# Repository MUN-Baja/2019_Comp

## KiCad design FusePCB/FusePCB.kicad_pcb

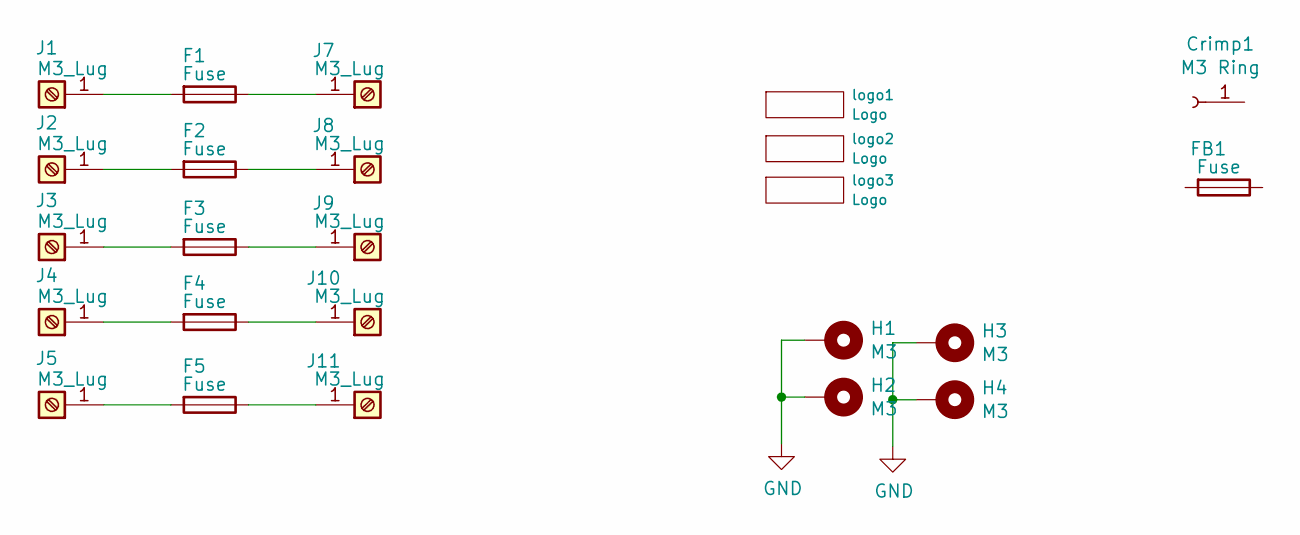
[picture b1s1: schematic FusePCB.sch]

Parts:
Crimp1: M3 Ring
F1, F2, F3, F4, F5: Fuse; Fuse_ATC_ATO_BLADE
FB1: Fuse
H1, H2, H3, H4: M3; 3.4mm_mounting_hole_SILK
J1, J2, J3, J4, J5, J7, J8, J9, J10, J11: M3_Lug; LVDC_M3_Lug
logo1, logo2: Logo; SN_BLOCK
logo3: Logo; KiCad-Logo_8mm_SilkScreen

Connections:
GND: H1.1, H2.1, H3.1, H4.1
unnamed: F1.1, J7.1
unnamed: F1.2, J1.1
unnamed: F2.1, J8.1
unnamed: F2.2, J2.1
unnamed: F3.1, J9.1
unnamed: F3.2, J3.1
unnamed: F4.1, J10.1
unnamed: F4.2, J4.1
unnamed: F5.1, J11.1
unnamed: F5.2, J5.1

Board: 2 copper layers, 22 parts (1 on the bottom side), 11 nets, no tracks yet.

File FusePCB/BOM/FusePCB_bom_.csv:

Component,Description,Part,References,Value,Footprint,Quantity Per PCB,Datasheet
1,"Generic connector, single row, 01x01, script generated (kicad-library-utils/schlib/autogen/connector/)",Conn_01x01_Female,Crimp1,M3 Ring,,10,277-11117-ND
2,Fuse,Fuse,F1 F2 F3 F4 F5,Fuse,Fuse_ATC_ATO_BLADE,10,36-3522-ND
4,"Generic screw terminal, single row, 01x01, script generated (kicad-library-utils/schlib/autogen/connector/)",Screw_Terminal_01x01,J1 J2 J3 J4 J5 J7 J8 J9 J10 J11,M3_Lug,LVDC_M3_Lug,10,36-7771-ND
,,3A,,,,3,F4193-ND
,,10A,,,,2,F4199-ND
,,20A,,,,2,F4201-ND
,,5A,,,,1,F4197-ND
,,15A,,,,1,F4200-ND
,,40A,,,,1,F4203-ND
,,7.5A,,,,1,F4198-ND
,,1A,,,,2,F4191-ND
,,,,,,,
,,,,,,,
,,,,,,,
,,,,,,,
,,,,,,,
,,,,,,,
,,,,,,,
,,,,,,,
,,,,,,,
,,,,,,,
,,,,,,,
Component Groups:,6,,,,,,
Component Count:,20,,,,,,
Fitted Components:,20,,,,,,
Number of PCBs:,1,,,,,,
Total components:,20,,,,,,
Schematic Version:,,,,,,,
Schematic Date:,,,,,,,
BoM Date:,5/25/2019 2:43,,,,,,
Schematic Source:,C:\projects\BAJA\FusePCB\FusePCB.sch,,,,,,
KiCad Version:,Eeschema (5.0.2)-1,,,,,,

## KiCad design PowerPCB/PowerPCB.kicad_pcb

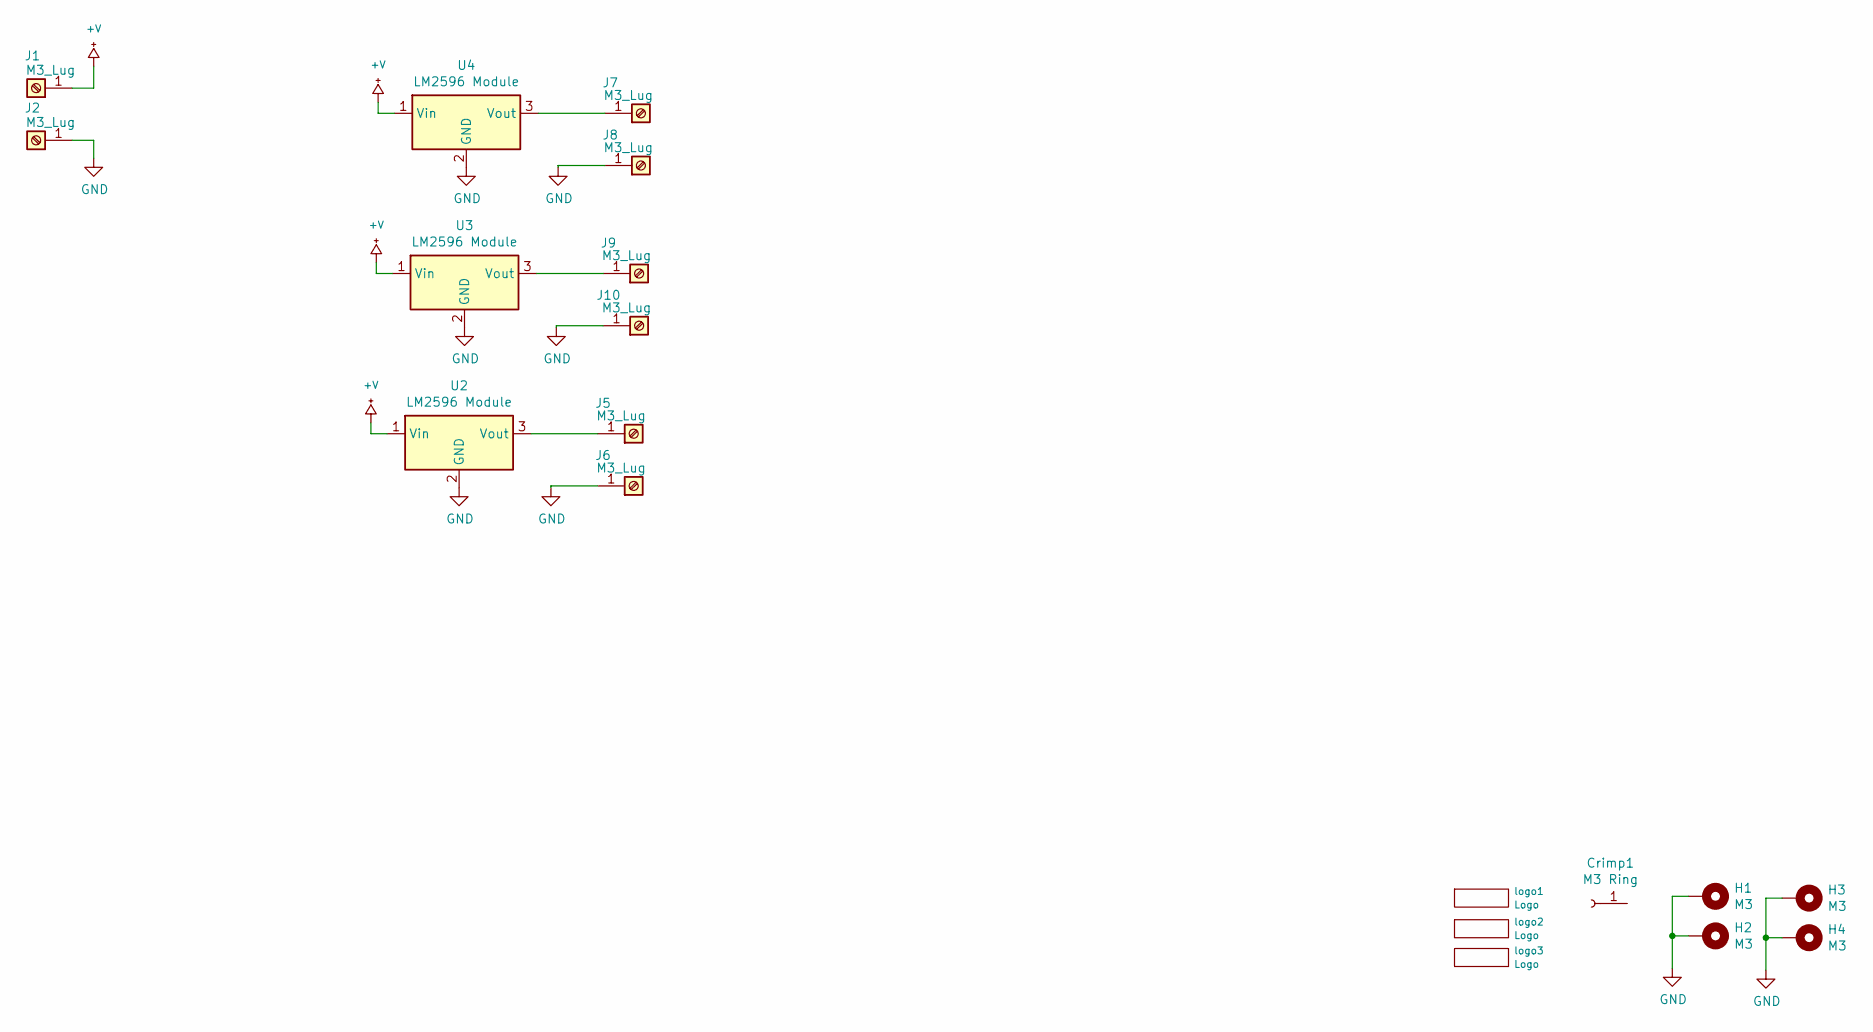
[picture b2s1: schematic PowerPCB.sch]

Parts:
Crimp1: M3 Ring
H1, H2, H3, H4: M3; 3.4mm_mounting_hole_SILK
J1, J2, J5, J6, J7, J8, J9, J10: M3_Lug; LVDC_M3_Lug
U2, U3, U4: LM2596 Module; LM2596_Module
logo1, logo2: Logo; SN_BLOCK
logo3: Logo; KiCad-Logo_8mm_SilkScreen

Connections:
+V: J1.1, U2.1 (Vin), U3.1 (Vin), U4.1 (Vin)
GND: H1.1, H2.1, H3.1, H4.1, J2.1, J6.1, J8.1, J10.1, U2.2 (GND), U3.2 (GND), U4.2 (GND)
unnamed: J5.1, U2.3 (Vout)
unnamed: J7.1, U4.3 (Vout)
unnamed: J9.1, U3.3 (Vout)

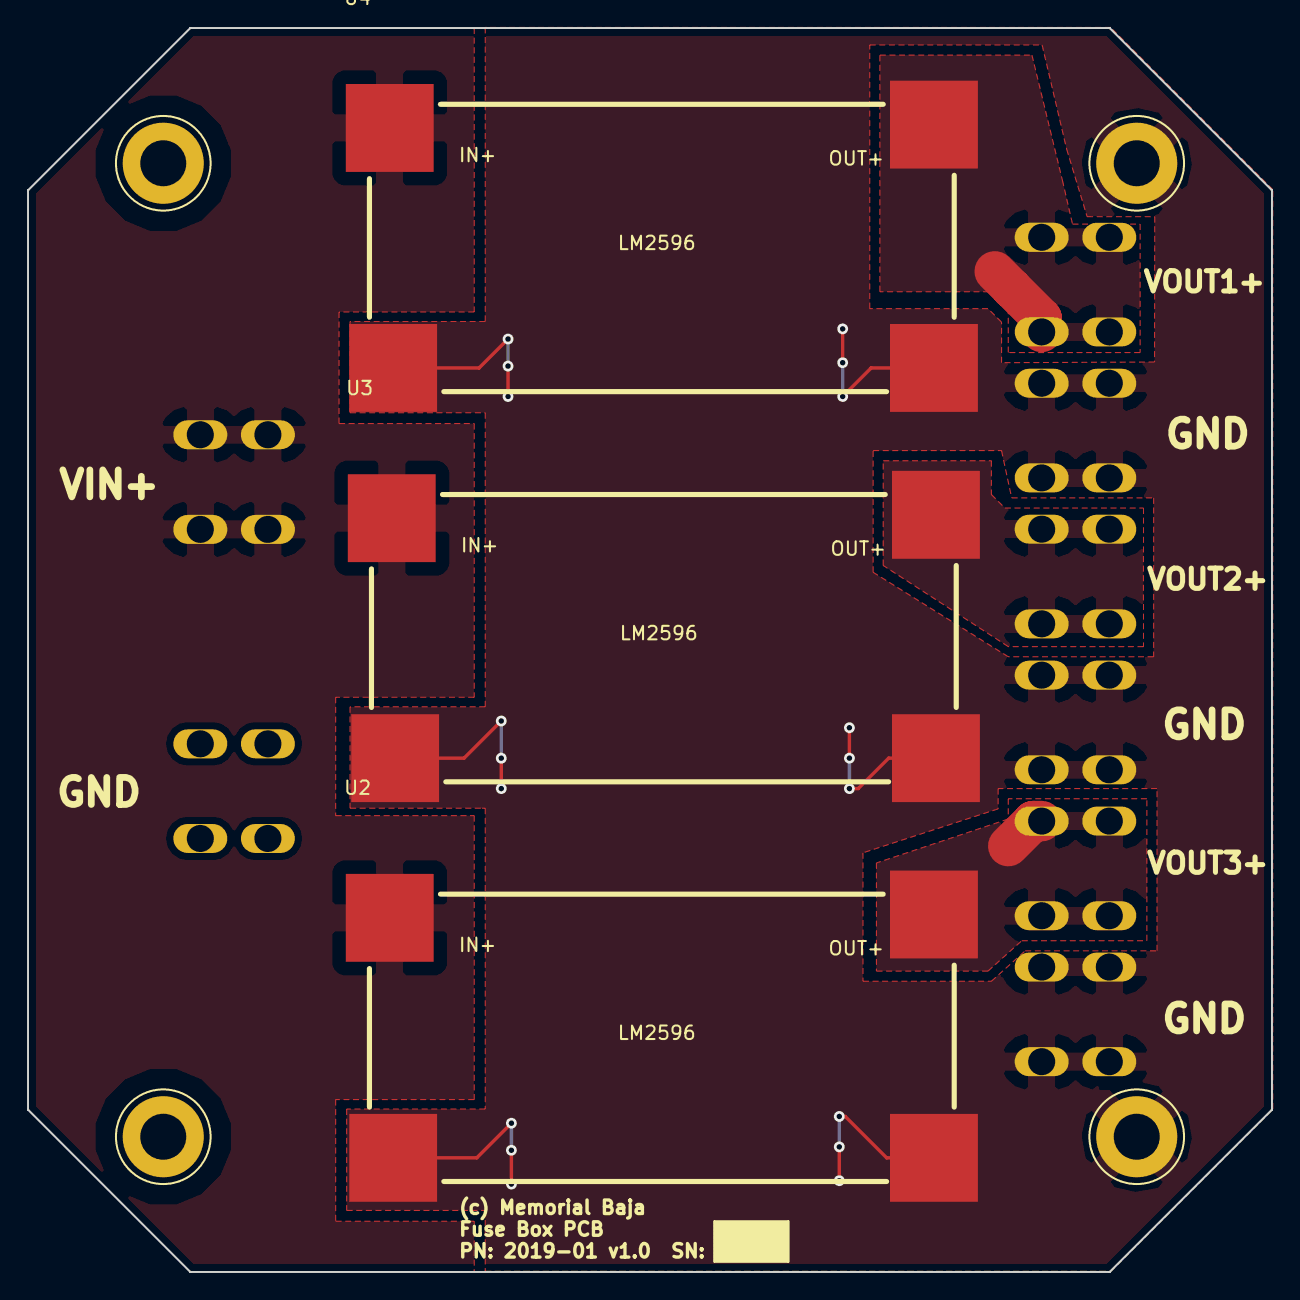
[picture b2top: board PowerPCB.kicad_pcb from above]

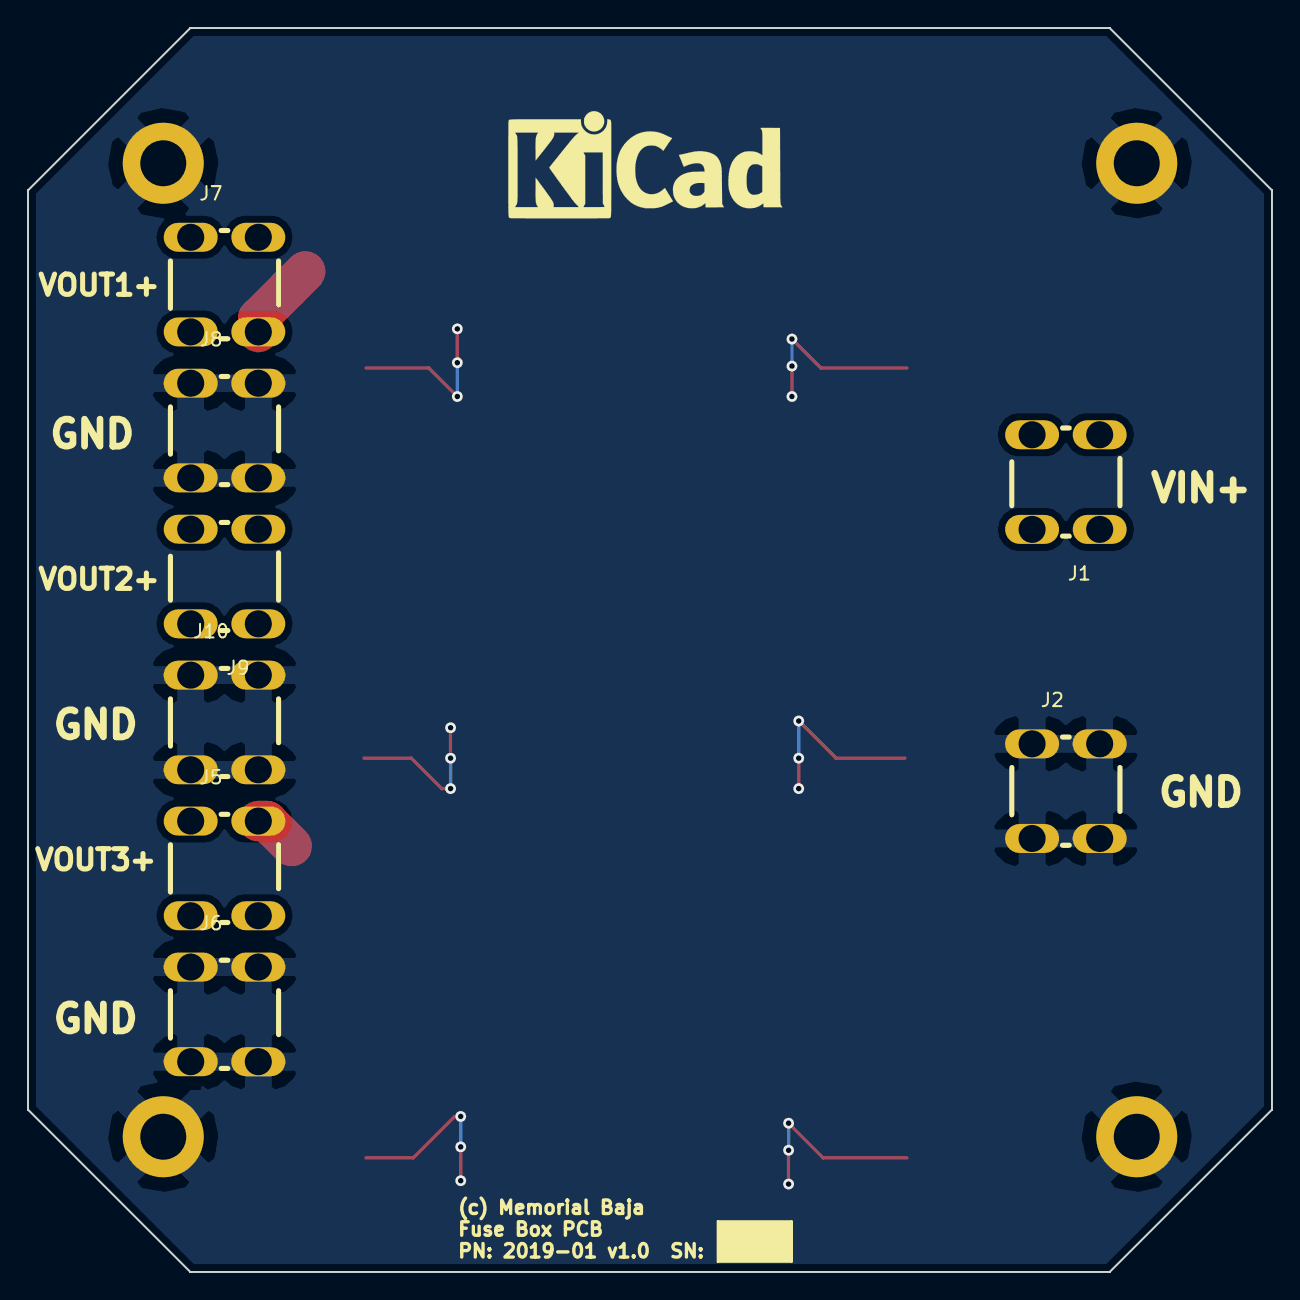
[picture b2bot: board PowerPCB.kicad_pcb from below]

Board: 2 copper layers, 92.0 x 92.0 mm, 18 parts (10 on the bottom side), 5 nets.

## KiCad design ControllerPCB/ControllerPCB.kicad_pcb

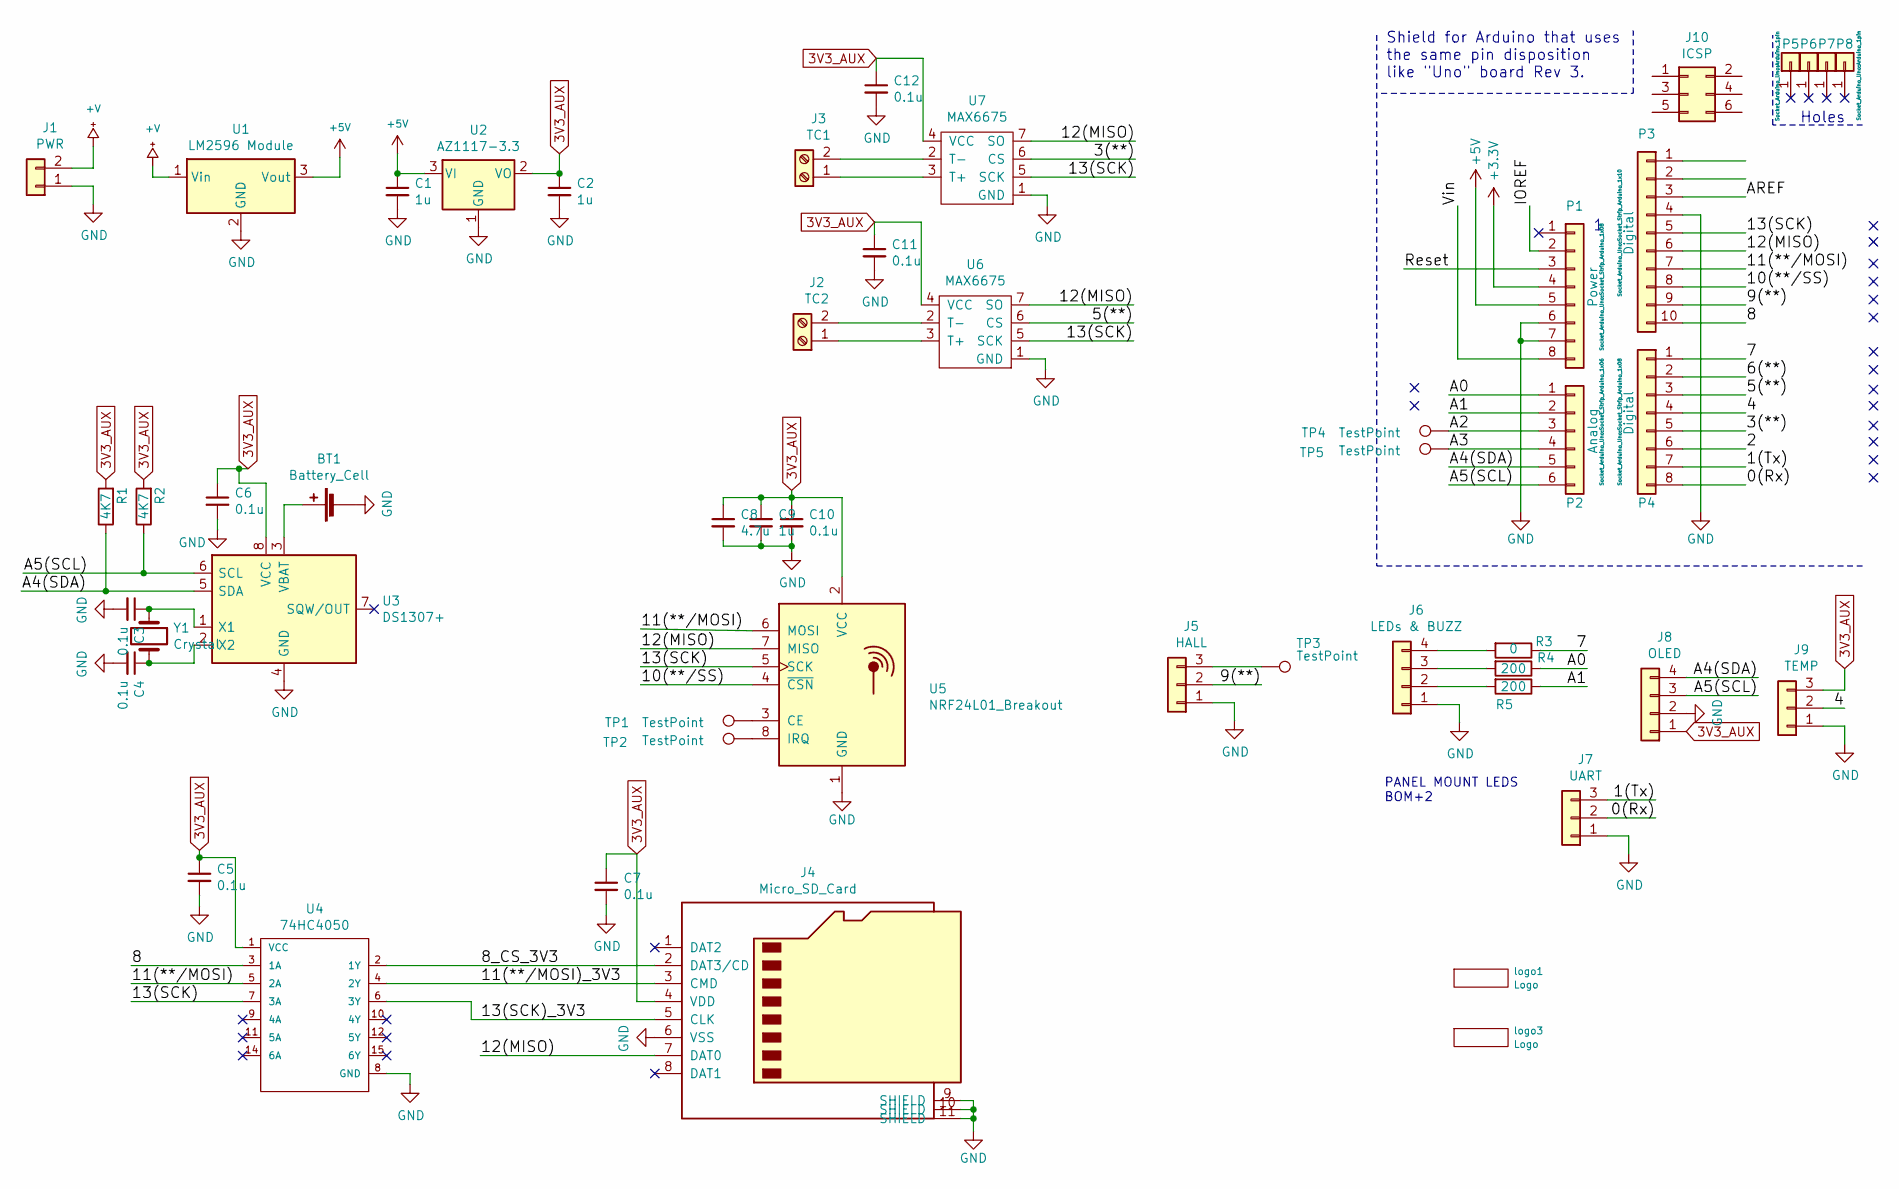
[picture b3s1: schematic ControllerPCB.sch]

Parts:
BT1: Battery_Cell; Keystone_3034_1x20mm-CoinCell
C1, C2, C9: 1u; SMD_pkg_0805
C3, C4: 0.1u; R_0402
C5, C6, C7, C10, C11, C12: 0.1u; SMD_pkg_0805
C8: 4.7u; SMD_pkg_0805
J1: PWR; JST_XH_S02B-XH-A_02x2.50mm_Angled
J2: TC2; TerminalBlock_RND_205-00232_1x02_P5.08mm_Horizontal
J3: TC1; TerminalBlock_RND_205-00232_1x02_P5.08mm_Horizontal
J4: Micro_SD_Card; Hirose_DM3D-SF
J5: HALL; Pin_Header_Straight_1x03_Pitch1.27mm
J6: LEDs & BUZZ; Pin_Header_Straight_1x04_Pitch1.27mm
J7: UART; Pin_Header_Straight_1x03_Pitch1.27mm
J8: OLED; Pin_Header_Straight_1x04_Pitch1.27mm
J9: TEMP; JST_XH_B03B-XH-A_03x2.50mm_Straight
J10: ICSP; Pin_Header_Straight_2x03_Pitch2.54mm
P1: Power; Socket_Strip_Arduino_1x08
P2: Analog; Socket_Strip_Arduino_1x06
P3: Digital; Socket_Strip_Arduino_1x10
P4: Digital; Socket_Strip_Arduino_1x08
P5, P6, P7, P8: CONN_01X01; Arduino_1pin
R1, R2: 4K7; SMD_pkg_0805
R3: 0; SMD_pkg_0805
R4, R5: 200; SMD_pkg_0805
TP1, TP2, TP3, TP4, TP5: TestPoint; Testpoint_circle_0.5mm
U1: LM2596 Module; LM2596_Module
U2: AZ1117-3.3; SOT-223-3_TabPin2
U3: DS1307+; SOIC-8_N
U4: 74HC4050; SOIC-16_N
U5: NRF24L01_Breakout; JST_XH_B08B-XH-A_08x2.50mm_Straight
U6, U7: MAX6675; SOIC-8_N
Y1: Crystal; Crystal_C38-LF_d3.0mm_l8.0mm_Horizontal
logo1: Logo; SN_BLOCK
logo3: Logo; KiCad-Logo_8mm_SilkScreen

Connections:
3V3_AUX: C2.1, C5.1, C6.1, C7.1, C8.1, C9.1, C10.1, C11.1, C12.1, J4.4 (VDD), J8.1, J9.3, R1.2, R2.2, U2.2 (VO), U3.8 (VCC), U4.1 (VCC), U5.2 (VCC), U6.4 (VCC), U7.4 (VCC)
+3V3: P1.4
+5V: C1.1, P1.5, U1.3 (Vout), U2.3 (VI)
+V: J1.2, U1.1 (Vin)
/0(Rx): J7.2, P4.8
/1(Tx): J7.3, P4.7
/2: P4.6
/3(**): P4.5, U7.6 (CS)
/4: J9.2, P4.4
/5(**): P4.3, U6.6 (CS)
/6(**): P4.2
/7: P4.1, R3.1
/8: P3.10, U4.3 (1A)
/8_CS_3V3: J4.2 (DAT3/CD), U4.2 (1Y)
/9(**): J5.2, P3.9
/10(**/SS): P3.8, U5.4 (~CSN)
/11(**/MOSI): P3.7, U4.5 (2A), U5.6 (MOSI)
/11(**/MOSI)_3V3: J4.3 (CMD), U4.4 (2Y)
/12(MISO): J4.7 (DAT0), P3.6, U5.7 (MISO), U6.7 (SO), U7.7 (SO)
/13(SCK): P3.5, U4.7 (3A), U5.5 (SCK), U6.5 (SCK), U7.5 (SCK)
/13(SCK)_3V3: J4.5 (CLK), U4.6 (3Y)
/A0: P2.1, R4.1
/A1: P2.2, R5.1
/A2: P2.3, TP4.1
/A3: P2.4, TP5.1
/A4(SDA): J8.4, P2.5, R1.1, U3.5 (SDA)
/A5(SCL): J8.3, P2.6, R2.1, U3.6 (SCL)
/AREF: P3.3
/IOREF: P1.2
/Reset: P1.3
/Vin: P1.8
GND: BT1.2 (-), C1.2, C2.2, C3.2, C4.2, C5.2, C6.2, C7.2, C8.2, C9.2, C10.2, C11.2, C12.2, J1.1, J4.6 (VSS), J4.9 (SHIELD), J4.10 (SHIELD), J4.11 (SHIELD), J5.1, J6.1, J7.1, J8.2, J9.1, P1.6, P1.7, P3.4, U1.2 (GND), U2.1 (GND), U3.4 (GND), U4.8 (GND), U5.1 (GND), U6.1 (GND), U7.1 (GND)
unnamed: BT1.1 (+), U3.3 (VBAT)
unnamed: C3.1, U3.1 (X1), Y1.1
unnamed: C4.1, U3.2 (X2), Y1.2
unnamed: J2.1, U6.3 (T+)
unnamed: J2.2, U6.2 (T-)
unnamed: J3.1, U7.3 (T+)
unnamed: J3.2, U7.2 (T-)
unnamed: J5.3, TP3.1
unnamed: J6.2, R5.2
unnamed: J6.3, R4.2
unnamed: J6.4, R3.2
unnamed: TP1.1, U5.3 (CE)
unnamed: TP2.1, U5.8 (IRQ)

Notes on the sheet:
Holes
Shield for Arduino that uses the same pin disposition like "Uno" board Rev 3.
PANEL MOUNT LEDS BOM+2

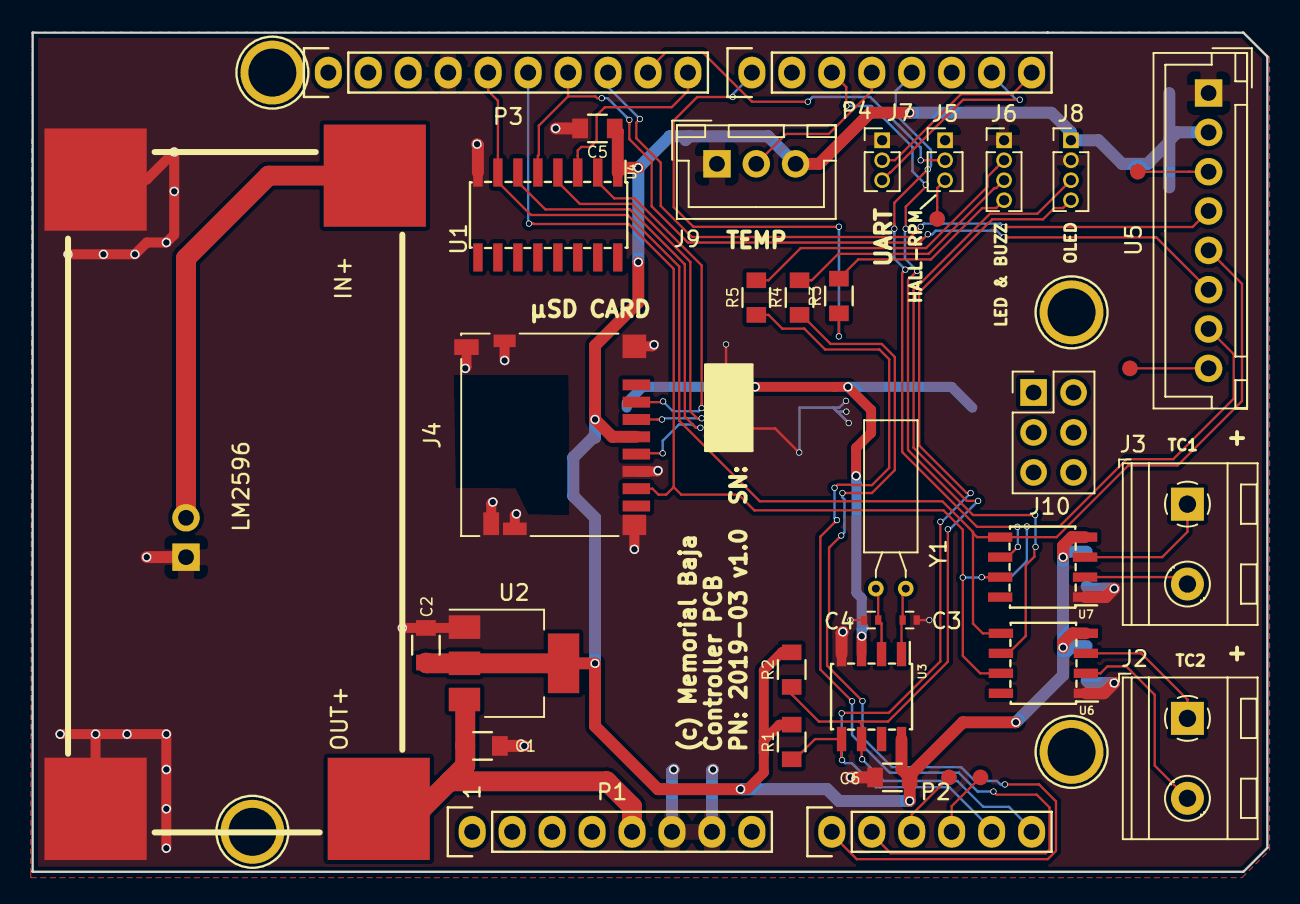
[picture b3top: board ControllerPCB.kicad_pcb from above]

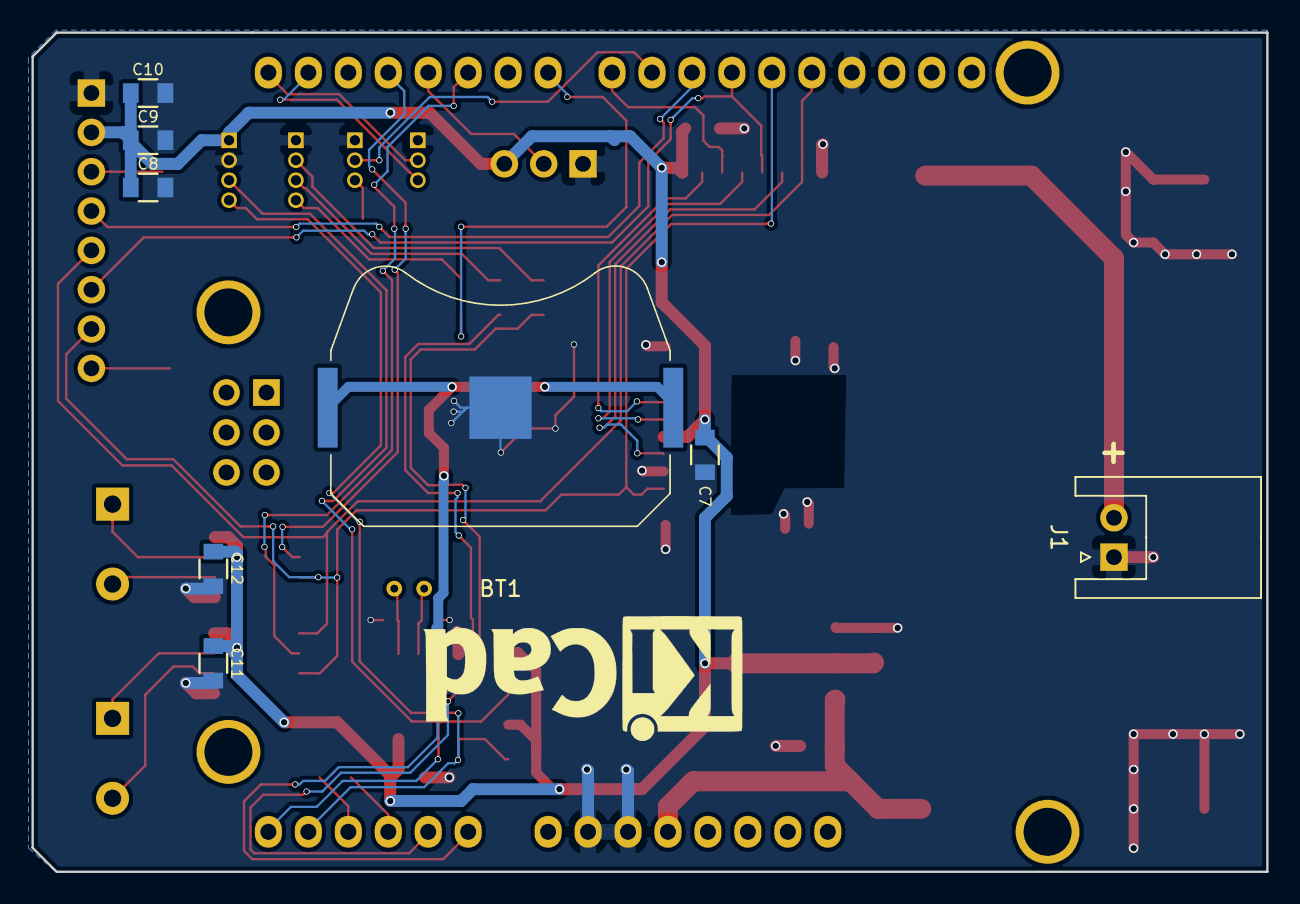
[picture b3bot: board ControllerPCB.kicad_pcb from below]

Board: 2 copper layers, 78.5 x 53.3 mm, 51 parts (9 on the bottom side), 38 nets.

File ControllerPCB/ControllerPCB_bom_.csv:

Component,Description,Part,References,Value,Footprint,Quantity Per PCB,Datasheet
1,Single-cell battery,Battery_Cell,BT1,Battery_Cell,Keystone_3034_1x20mm-CoinCell,1,36-3034-ND
2,"Unpolarized capacitor, small symbol",C_Small,C5 C6 C7 C10 C11 C12,0.1u,SMD_pkg_0805,6,~
3,"Unpolarized capacitor, small symbol",C_Small,C3 C4,0.1u,R_0402,2,~
4,"Unpolarized capacitor, small symbol",C_Small,C1 C2 C9,1u,SMD_pkg_0805,3,~
5,"Unpolarized capacitor, small symbol",C_Small,C8,4.7u,SMD_pkg_0805,1,~
6,"Generic connector, single row, 01x03, script generated (kicad-library-utils/schlib/autogen/connector/)",Conn_01x03,J5,HALL,Pin_Header_Straight_1x03_Pitch1.27mm,1,~
7,"Generic connector, double row, 02x03, odd/even pin numbering scheme (row 1 odd numbers, row 2 even numbers), script generated (kicad-library-utils/schlib/autogen/connector/)",Conn_02x03_Odd_Even,J10,ICSP,Pin_Header_Straight_2x03_Pitch2.54mm,1,~
8,"Generic connector, single row, 01x04, script generated (kicad-library-utils/schlib/autogen/connector/)",Conn_01x04,J6,LEDs & BUZZ,Pin_Header_Straight_1x04_Pitch1.27mm,1,~
9,Micro SD Card Socket,Micro_SD_Card,J4,Micro_SD_Card,Hirose_DM3D-SF,1,HR1941CT-ND
10,"Generic connector, single row, 01x04, script generated (kicad-library-utils/schlib/autogen/connector/)",Conn_01x04,J8,OLED,Pin_Header_Straight_1x04_Pitch1.27mm,1,~
11,"Generic connector, single row, 01x02, script generated (kicad-library-utils/schlib/autogen/connector/)",Conn_01x02,J1,PWR,JST_XH_S02B-XH-A_02x2.50mm_Angled,1,~
12,"Generic screw terminal, single row, 01x02, script generated (kicad-library-utils/schlib/autogen/connector/)",Screw_Terminal_01x02,J3,TC1,TerminalBlock_RND_205-00232_1x02_P5.08mm_Horizontal,1,~
13,"Generic screw terminal, single row, 01x02, script generated (kicad-library-utils/schlib/autogen/connector/)",Screw_Terminal_01x02,J2,TC2,TerminalBlock_RND_205-00232_1x02_P5.08mm_Horizontal,1,~
14,"Generic connector, single row, 01x03, script generated (kicad-library-utils/schlib/autogen/connector/)",Conn_01x03,J9,TEMP,JST_XH_B03B-XH-A_03x2.50mm_Straight,1,~
15,"Generic connector, single row, 01x03, script generated (kicad-library-utils/schlib/autogen/connector/)",Conn_01x03,J7,UART,Pin_Header_Straight_1x03_Pitch1.27mm,1,~
16,"Generic connector, single row, 01x06, script generated (kicad-library-utils/schlib/autogen/connector/)",Conn_01x06,P2,Analog,Socket_Strip_Arduino_1x06,1,
17,"Generic connector, single row, 01x01, script generated (kicad-library-utils/schlib/autogen/connector/)",Conn_01x01,P5 P6 P7 P8,CONN_01X01,Arduino_1pin,4,
18,"Generic connector, single row, 01x10, script generated (kicad-library-utils/schlib/autogen/connector/)",Conn_01x10,P3,Digital,Socket_Strip_Arduino_1x10,1,
19,"Generic connector, single row, 01x08, script generated (kicad-library-utils/schlib/autogen/connector/)",Conn_01x08,P4,Digital,Socket_Strip_Arduino_1x08,1,
20,"Generic connector, single row, 01x08, script generated (kicad-library-utils/schlib/autogen/connector/)",Conn_01x08,P1,Power,Socket_Strip_Arduino_1x08,1,
21,Resistor,R,R3,0,SMD_pkg_0805,1,~
22,Resistor,R,R4 R5,330,SMD_pkg_0805,2,~
23,Resistor,R,R1 R2,4K7,SMD_pkg_0805,2,~
24,,74HC4050,U4,74HC4050,SOIC-16_N,1,1727-6331-1-ND
25,"1A 20V Fixed LDO Linear Regulator, 1.2V, SOT-89/SOT-223/TO-220/TO-252/TO-263",AZ1117-3.3,U2,AZ1117-3.3,SOT-223-3_TabPin2,1,AZ1117EH-3.3TRG1DICT-ND
26,"64 x 8, Serial, I2C Real-time clock, 4.5V to 5.5V VCC, 0°C to +70°C, DIP-8",DS1307+,U3,DS1307+,SOIC-8_N,1,DS1307Z+T&RCT-ND
27,"1A step-down regulator module, fixed 5V output voltage, 5-36V input voltage, -40°C to +85°C temperature range, TO-220 compatible LM78xx replacement",TSR_1-2412,U1,LM2596 Module,LM2596_Module,1,http://www.tracopower.com/products/tsr1.pdf
28,,MAX6675,U6 U7,MAX6675,SOIC-8_N,2,
29,"Ultra low power 2.4GHz RF Transceiver, Carrier PCB",NRF24L01_Breakout,U5,NRF24L01_Breakout,JST_XH_B08B-XH-A_08x2.50mm_Straight,1,http://www.nordicsemi.com/eng/content/download/2730/34105/fi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
30,Two pin crystal,Crystal,Y1,Crystal,Crystal_C38-LF_d3.0mm_l8.0mm_Horizontal,1,535-9034-ND
31,,Logo,logo1,Logo,SN_BLOCK,1,
32,,Logo,logo3,Logo,KiCad-Logo_8mm_SilkScreen,1,





Component Groups:,32
Component Count:,46
Fitted Components:,46
Number of PCBs:,1
Total components:,46
Schematic Version:,
Schematic Date:,lun. 30 mars 2015
BoM Date:,5/26/2019 9:39:06 AM
Schematic Source:,C:\projects\BAJA\ControllerPCB\ControllerPCB.sch
KiCad Version:,Eeschema (5.0.2)-1

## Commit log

2019-05-27 Uploading 3 comp PCBs finished
2019-05-29 test models
2019-06-01 added gcode for printed models
2019-06-01 Adding code template and pdf sch
2019-06-06 added Mohammed's RF template code
